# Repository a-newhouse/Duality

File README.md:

# Disclaimer
This is my first attempt, with [Numb](https://github.com/a-newhouse/Numb), to make a fully functional keyboard from A to Z. 
# Schematic
# PCB
# 3D modeling
# BOM
# Assembly
# QMK Firmware

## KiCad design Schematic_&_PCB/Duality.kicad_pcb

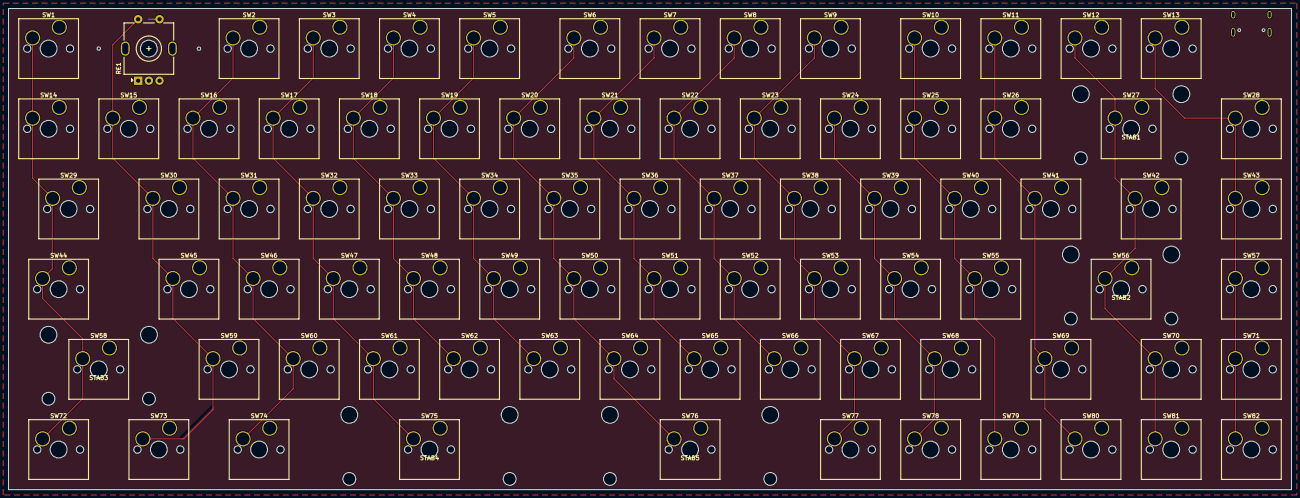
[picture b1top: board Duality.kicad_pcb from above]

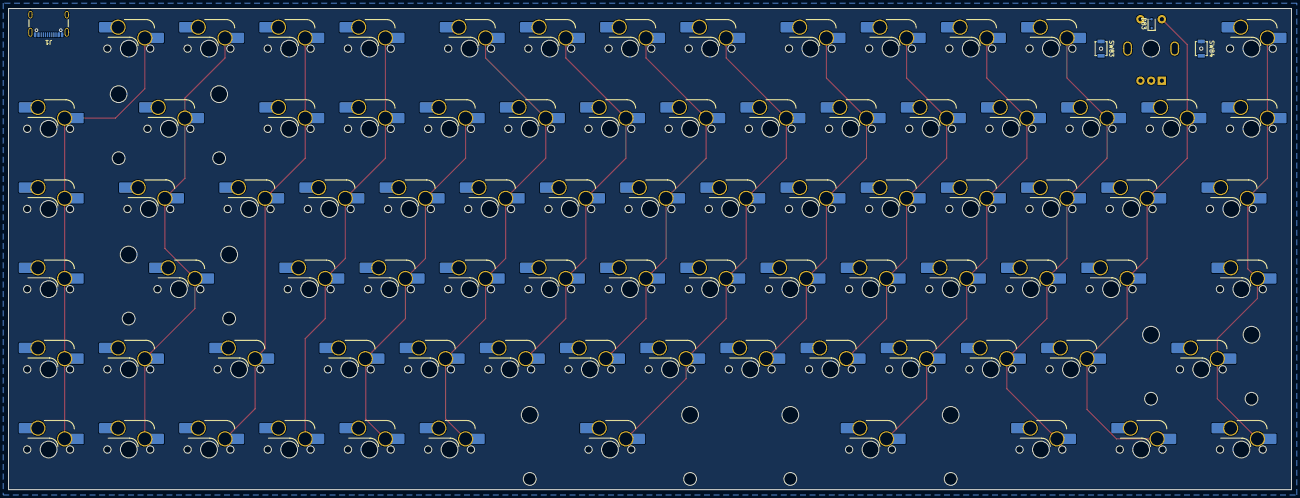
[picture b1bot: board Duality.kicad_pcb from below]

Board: 2 copper layers, 304.8 x 114.3 mm, 92 parts (86 on the bottom side), 20 nets.

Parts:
D83: 1N4148WS; D_SOD-323
J1: GCT USB4105; USB_C_Receptacle_GCT_USB4105-xx-A_16P_TopMnt_Horizontal
RE1: RotaryEncoder_Switch_MP; EC11E-Switch_Vertical_H11mm
STAB1, STAB2, STAB3: Stablizer_2U; Stabilizer_Cherry_MX_2.00u
STAB4, STAB5: Stablizer_3U; Stabilizer_Cherry_MX_3.00u
SW1: ESC; SW_Hotswap_Kailh_MX_Plated_1.00u
SW2: F1; SW_Hotswap_Kailh_MX_Plated_1.00u
SW3: F2; SW_Hotswap_Kailh_MX_Plated_1.00u
SW4: F3; SW_Hotswap_Kailh_MX_Plated_1.00u
SW5: F4; SW_Hotswap_Kailh_MX_Plated_1.00u
SW6: F5; SW_Hotswap_Kailh_MX_Plated_1.00u
SW7: F6; SW_Hotswap_Kailh_MX_Plated_1.00u
SW8: F7; SW_Hotswap_Kailh_MX_Plated_1.00u
SW9: F8; SW_Hotswap_Kailh_MX_Plated_1.00u
SW10: F9; SW_Hotswap_Kailh_MX_Plated_1.00u
SW11: F10; SW_Hotswap_Kailh_MX_Plated_1.00u
SW12: F11; SW_Hotswap_Kailh_MX_Plated_1.00u
SW13: F12; SW_Hotswap_Kailh_MX_Plated_1.00u
SW14: `; SW_Hotswap_Kailh_MX_Plated_1.00u
SW15: 1; SW_Hotswap_Kailh_MX_Plated_1.00u
SW16: 2; SW_Hotswap_Kailh_MX_Plated_1.00u
SW17: 3; SW_Hotswap_Kailh_MX_Plated_1.00u
SW18: 4; SW_Hotswap_Kailh_MX_Plated_1.00u
SW19: 5; SW_Hotswap_Kailh_MX_Plated_1.00u
SW20: 6; SW_Hotswap_Kailh_MX_Plated_1.00u
SW21: 7; SW_Hotswap_Kailh_MX_Plated_1.00u
SW22: 8; SW_Hotswap_Kailh_MX_Plated_1.00u
SW23: 9; SW_Hotswap_Kailh_MX_Plated_1.00u
SW24: 0; SW_Hotswap_Kailh_MX_Plated_1.00u
SW25: -; SW_Hotswap_Kailh_MX_Plated_1.00u
SW26: =; SW_Hotswap_Kailh_MX_Plated_1.00u
SW27: Backspace; SW_Hotswap_Kailh_MX_Plated_2.00u
SW28: Delete; SW_Hotswap_Kailh_MX_Plated_1.00u
SW29: Tab; SW_Hotswap_Kailh_MX_Plated_1.50u
SW30: Q; SW_Hotswap_Kailh_MX_Plated_1.00u
SW31: W; SW_Hotswap_Kailh_MX_Plated_1.00u
SW32: E; SW_Hotswap_Kailh_MX_Plated_1.00u
SW33: R; SW_Hotswap_Kailh_MX_Plated_1.00u
SW34: T; SW_Hotswap_Kailh_MX_Plated_1.00u
SW35: Y; SW_Hotswap_Kailh_MX_Plated_1.00u
SW36: U; SW_Hotswap_Kailh_MX_Plated_1.00u
SW37: I; SW_Hotswap_Kailh_MX_Plated_1.00u
SW38: O; SW_Hotswap_Kailh_MX_Plated_1.00u
SW39: P; SW_Hotswap_Kailh_MX_Plated_1.00u
SW40: [; SW_Hotswap_Kailh_MX_Plated_1.00u
SW41: ]; SW_Hotswap_Kailh_MX_Plated_1.00u
SW42: \; SW_Hotswap_Kailh_MX_Plated_1.50u
SW43: Home; SW_Hotswap_Kailh_MX_Plated_1.00u
SW44: Caps Lock; SW_Hotswap_Kailh_MX_Plated_1.25u
SW45: A; SW_Hotswap_Kailh_MX_Plated_1.00u
SW46: S; SW_Hotswap_Kailh_MX_Plated_1.00u
SW47: D; SW_Hotswap_Kailh_MX_Plated_1.00u
SW48: F; SW_Hotswap_Kailh_MX_Plated_1.00u
SW49: G; SW_Hotswap_Kailh_MX_Plated_1.00u
SW50: H; SW_Hotswap_Kailh_MX_Plated_1.00u
SW51: J; SW_Hotswap_Kailh_MX_Plated_1.00u
SW52: K; SW_Hotswap_Kailh_MX_Plated_1.00u
SW53: L; SW_Hotswap_Kailh_MX_Plated_1.00u
SW54: ;; SW_Hotswap_Kailh_MX_Plated_1.00u
SW55: '; SW_Hotswap_Kailh_MX_Plated_1.00u
SW56: Enter; SW_Hotswap_Kailh_MX_Plated_2.25u
SW57: Page Up; SW_Hotswap_Kailh_MX_Plated_1.00u
SW58: Shift; SW_Hotswap_Kailh_MX_Plated_2.25u
SW59: Z; SW_Hotswap_Kailh_MX_Plated_1.00u
SW60: X; SW_Hotswap_Kailh_MX_Plated_1.00u
SW61: C; SW_Hotswap_Kailh_MX_Plated_1.00u
SW62: V; SW_Hotswap_Kailh_MX_Plated_1.00u
SW63: B; SW_Hotswap_Kailh_MX_Plated_1.00u
SW64: N; SW_Hotswap_Kailh_MX_Plated_1.00u
SW65: M; SW_Hotswap_Kailh_MX_Plated_1.00u
SW66: ,; SW_Hotswap_Kailh_MX_Plated_1.00u
SW67: .; SW_Hotswap_Kailh_MX_Plated_1.00u
SW68: /; SW_Hotswap_Kailh_MX_Plated_1.00u
SW69: Shift; SW_Hotswap_Kailh_MX_Plated_1.75u
SW70: ↑; SW_Hotswap_Kailh_MX_Plated_1.00u
SW71: Page Down; SW_Hotswap_Kailh_MX_Plated_1.00u
SW72: Control; SW_Hotswap_Kailh_MX_Plated_1.25u
SW73: Windows; SW_Hotswap_Kailh_MX_Plated_1.25u
SW74: Alt; SW_Hotswap_Kailh_MX_Plated_1.25u
SW75, SW76: Space; SW_Hotswap_Kailh_MX_Plated_3.00u
SW77: Control; SW_Hotswap_Kailh_MX_Plated_1.00u
SW78: Alt; SW_Hotswap_Kailh_MX_Plated_1.00u
SW79: Menu; SW_Hotswap_Kailh_MX_Plated_1.00u
SW80: ←; SW_Hotswap_Kailh_MX_Plated_1.00u
SW81: ↓; SW_Hotswap_Kailh_MX_Plated_1.00u
SW82: →; SW_Hotswap_Kailh_MX_Plated_1.00u
SW83: ~{RESET}; SW_SPST_B3U-1000P-B
SW84: ~{USB_BOOT}; SW_SPST_B3U-1000P-B

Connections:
+5V: J1.A4 (VBUS), J1.A9 (VBUS), J1.B4 (VBUS), J1.B9 (VBUS)
COL1: SW1.1 (A), SW14.1 (A), SW29.1 (A), SW44.1 (A), SW58.1 (A), SW72.1 (A)
COL2: RE1.S2, SW15.1 (A), SW30.1 (A), SW45.1 (A), SW59.1 (A), SW73.1 (A)
COL3: SW2.1 (A), SW16.1 (A), SW31.1 (A), SW46.1 (A), SW60.1 (A), SW74.1 (A)
COL4: SW3.1 (A), SW17.1 (A), SW32.1 (A), SW47.1 (A), SW61.1 (A), SW75.1 (A)
COL5: SW4.1 (A), SW18.1 (A), SW33.1 (A), SW48.1 (A), SW62.1 (A)
COL6: SW5.1 (A), SW19.1 (A), SW34.1 (A), SW49.1 (A), SW63.1 (A)
COL7: SW6.1 (A), SW20.1 (A), SW35.1 (A), SW50.1 (A), SW64.1 (A), SW76.1 (A)
COL8: SW7.1 (A), SW21.1 (A), SW36.1 (A), SW51.1 (A), SW65.1 (A)
COL9: SW8.1 (A), SW22.1 (A), SW37.1 (A), SW52.1 (A), SW66.1 (A)
COL10: SW9.1 (A), SW23.1 (A), SW38.1 (A), SW53.1 (A), SW67.1 (A), SW77.1 (A)
COL11: SW24.1 (A), SW39.1 (A), SW54.1 (A), SW68.1 (A), SW78.1 (A)
COL12: SW10.1 (A), SW25.1 (A), SW40.1 (A), SW55.1 (A), SW79.1 (A)
COL13: SW11.1 (A), SW26.1 (A), SW41.1 (A), SW69.1 (A), SW80.1 (A)
COL14: SW12.1 (A), SW27.1 (A), SW42.1 (A), SW56.1 (A), SW70.1 (A), SW81.1 (A)
COL15: SW13.1 (A), SW28.1 (A), SW43.1 (A), SW57.1 (A), SW71.1 (A), SW82.1 (A)
GND: J1.A1 (GND), J1.A12 (GND), J1.B1 (GND), J1.B12 (GND), J1.S1 (SHIELD), RE1.C, RE1.MP, SW83.1 (A), SW84.1 (A)
unnamed: D83.2 (A), RE1.S1
unnamed: J1.A6 (D+), J1.B6 (D+)
unnamed: J1.A7 (D-), J1.B7 (D-)

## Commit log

2024-12-15 started the schematic
2024-12-15 Started PCB
2024-12-15 continuing the pcb
2024-12-15 continuing pcb
2024-12-16 I think i will change the MCU
